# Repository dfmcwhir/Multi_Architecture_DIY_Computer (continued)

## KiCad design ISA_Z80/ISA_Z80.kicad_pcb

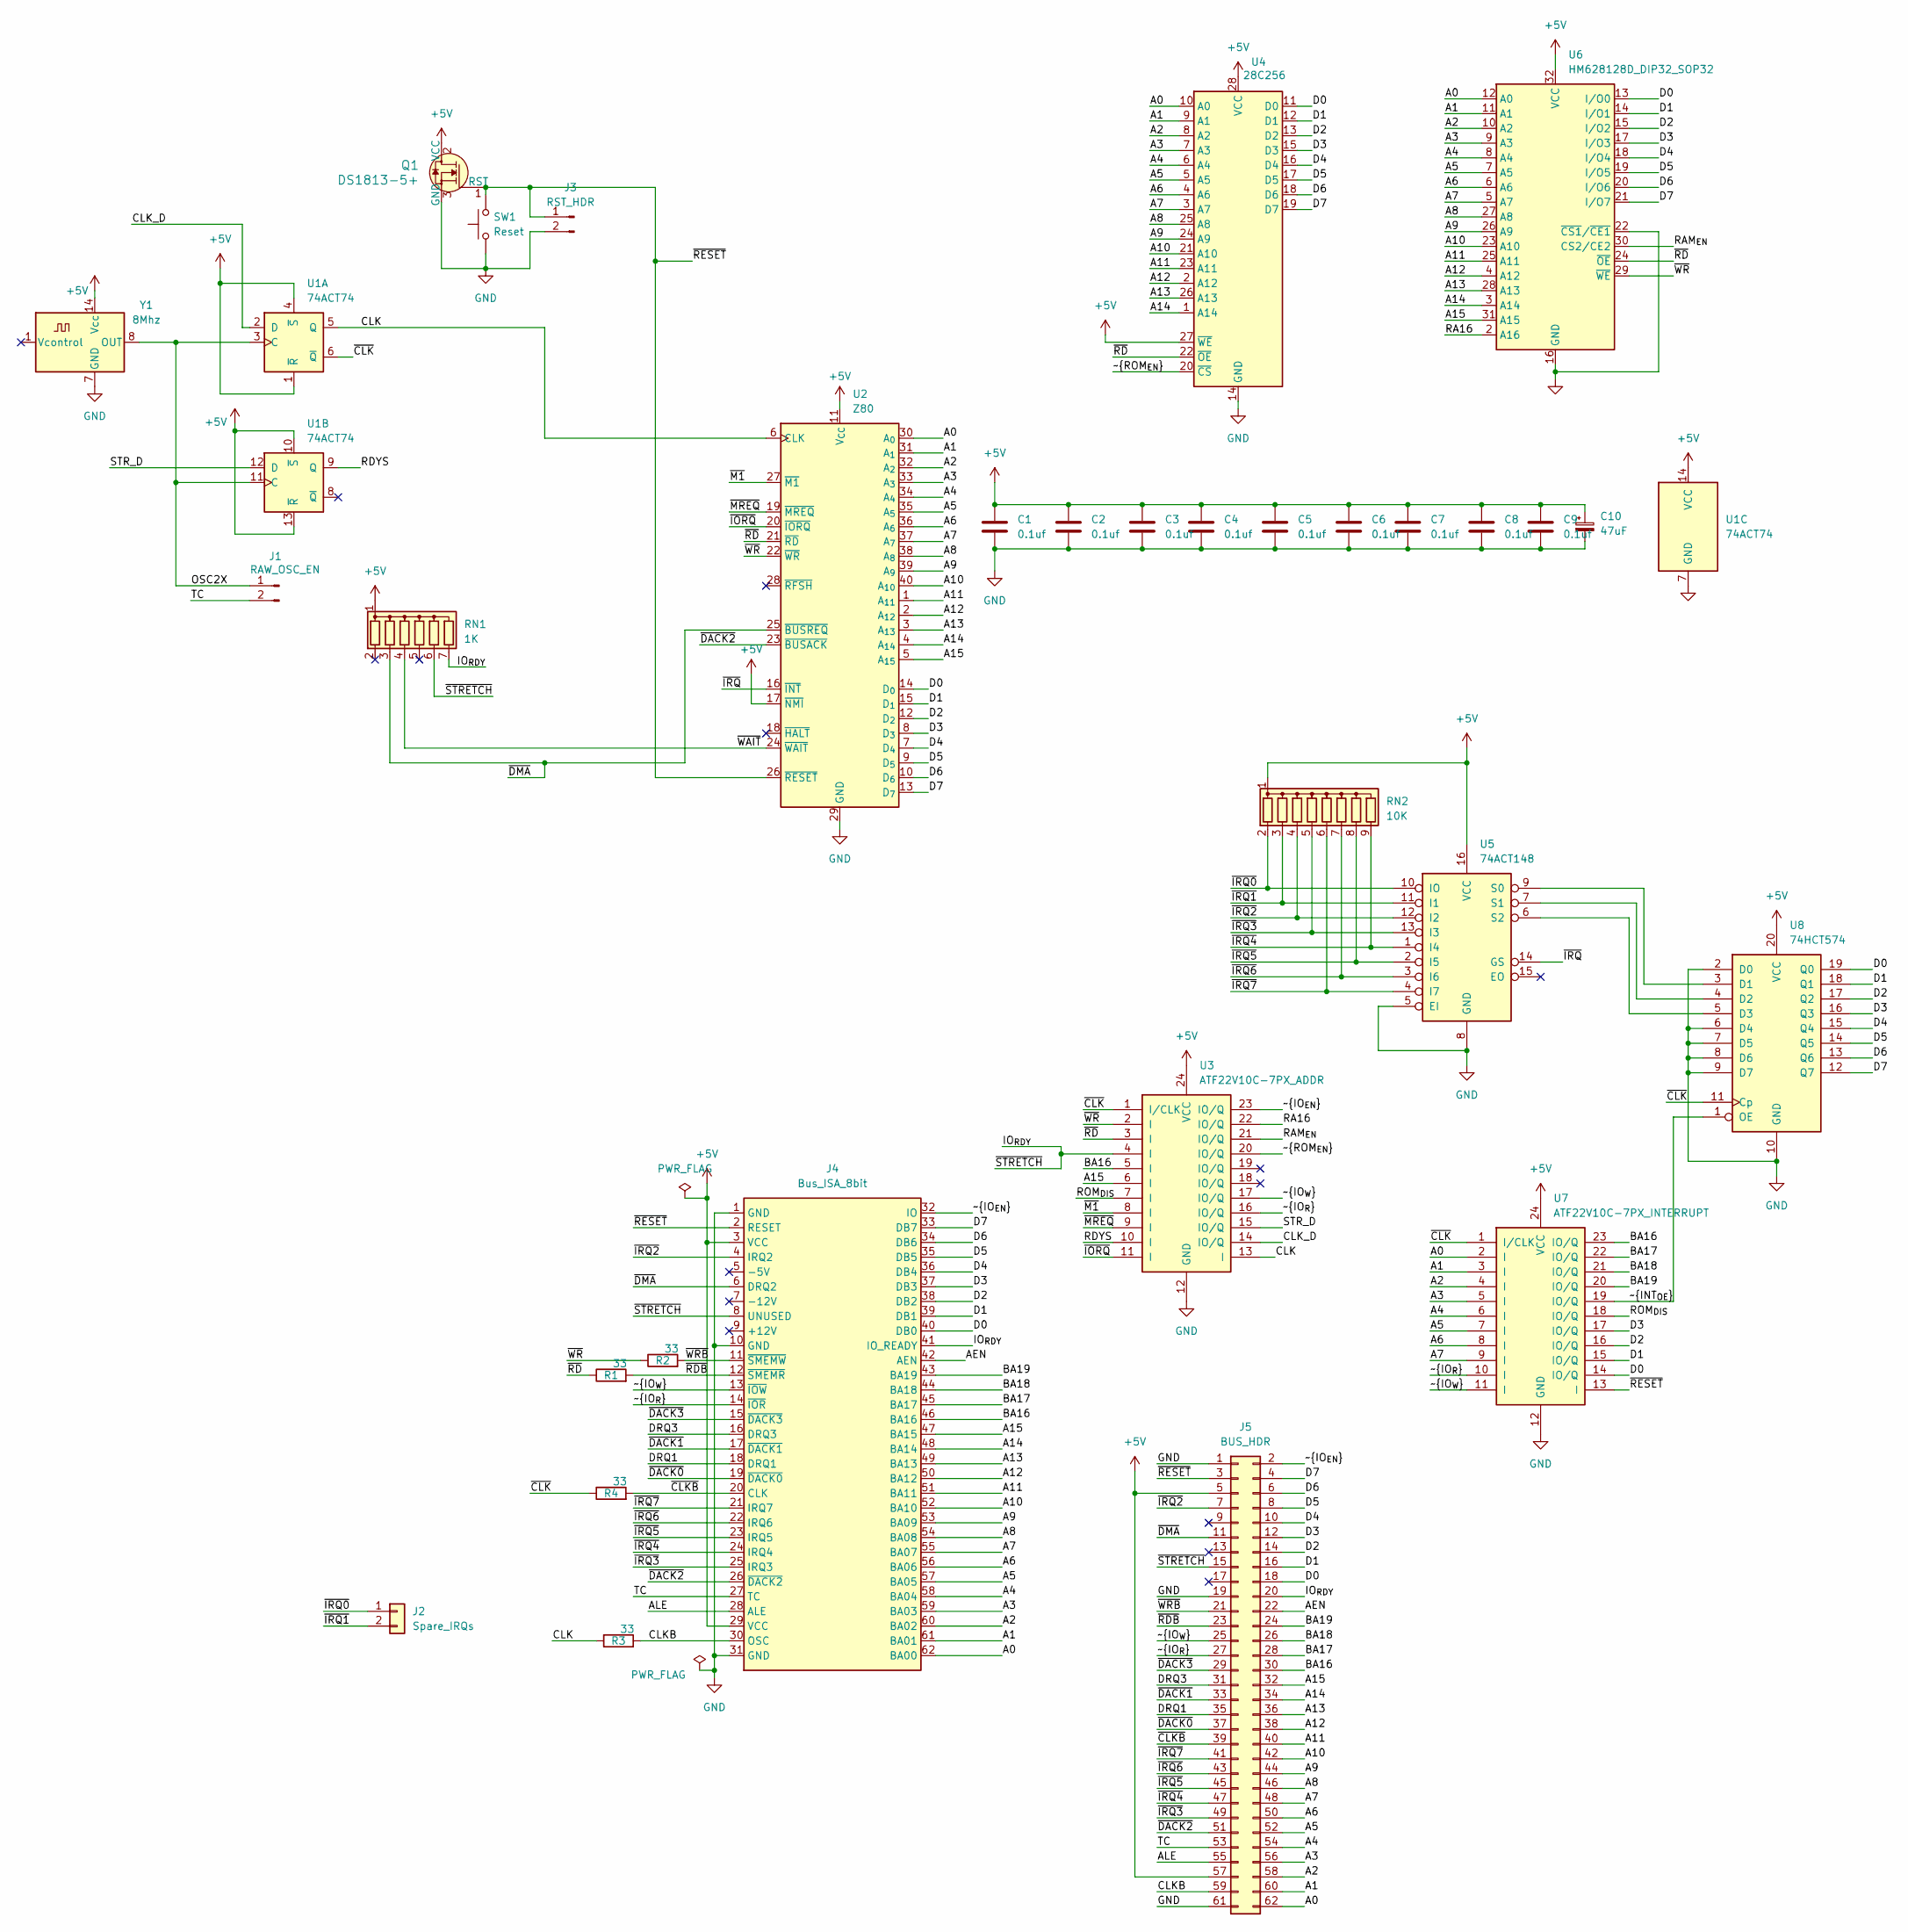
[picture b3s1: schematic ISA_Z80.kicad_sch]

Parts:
C1, C2, C3, C4, C5, C6, C7, C8, C9: 0.1uf; C_Disc_D4.7mm_W2.5mm_P5.00mm
C10: 47uF; CP_Radial_D5.0mm_P2.00mm
J1: RAW_OSC_EN; PinHeader_1x02_P2.54mm_Vertical
J2: Spare_IRQs; PinHeader_1x02_P2.54mm_Vertical
J3: RST_HDR; PinHeader_1x02_P2.54mm_Vertical
J4: Bus_ISA_8bit; BUS_8-bit_ISA
J5: BUS_HDR; PinHeader_2x31_P2.54mm_Vertical
Q1: DS1813-5+; TO-92L_Wide; MPN DS1813-5+-ND; Digi-Key_PN DS1813-5+-ND
R1, R2, R3, R4: 33; R_Axial_DIN0207_L6.3mm_D2.5mm_P10.16mm_Horizontal
RN1: 1K; R_Array_SIP7
RN2: 10K; R_Array_SIP9
SW1: Reset; SW_PUSH_6mm
U1: 74ACT74; DIP-14_W7.62mm
U2: Z80; DIP-40_W15.24mm
U3: ATF22V10C-7PX_ADDR; DIP-24_W7.62mm
U4: 28C256; DIP-28_W15.24mm
U5: 74ACT148; DIP-16_W7.62mm
U6: HM628128D_DIP32_SOP32; DIP-32_W15.24mm
U7: ATF22V10C-7PX_INTERRUPT; DIP-24_W7.62mm
U8: 74HCT574; DIP-20_W7.62mm
Y1: 8Mhz; Oscillator_DIP-14

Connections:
+5V: C1.1, C2.1, C3.1, C4.1, C5.1, C6.1, C7.1, C8.1, C9.1, C10.1, J4.3 (VCC), J4.29 (VCC), J5.5, J5.57, Q1.2 (VCC), RN1.1 (common), RN2.1 (common), U1.1 (~R), U1.4 (~S), U1.10 (~S), U1.13 (~R), U1.14 (VCC), U2.11 (V_{CC}), U2.17 (~NMI), U3.24 (VCC), U4.27 (~WE), U4.28 (VCC), U5.16 (VCC), U6.32 (VCC), U7.24 (VCC), U8.20 (VCC), Y1.14 (Vcc)
/A0: J4.62 (BA00), J5.62, U2.30 (A_{0}), U4.10 (A0), U6.12 (A0), U7.2 (I)
/A1: J4.61 (BA01), J5.60, U2.31 (A_{1}), U4.9 (A1), U6.11 (A1), U7.3 (I)
/A2: J4.60 (BA02), J5.58, U2.32 (A_{2}), U4.8 (A2), U6.10 (A2), U7.4 (I)
/A3: J4.59 (BA03), J5.56, U2.33 (A_{3}), U4.7 (A3), U6.9 (A3), U7.5 (I)
/A4: J4.58 (BA04), J5.54, U2.34 (A_{4}), U4.6 (A4), U6.8 (A4), U7.6 (I)
/A5: J4.57 (BA05), J5.52, U2.35 (A_{5}), U4.5 (A5), U6.7 (A5), U7.7 (I)
/A6: J4.56 (BA06), J5.50, U2.36 (A_{6}), U4.4 (A6), U6.6 (A6), U7.8 (I)
/A7: J4.55 (BA07), J5.48, U2.37 (A_{7}), U4.3 (A7), U6.5 (A7), U7.9 (I)
/A8: J4.54 (BA08), J5.46, U2.38 (A_{8}), U4.25 (A8), U6.27 (A8)
/A9: J4.53 (BA09), J5.44, U2.39 (A_{9}), U4.24 (A9), U6.26 (A9)
/A10: J4.52 (BA10), J5.42, U2.40 (A_{10}), U4.21 (A10), U6.23 (A10)
/A11: J4.51 (BA11), J5.40, U2.1 (A_{11}), U4.23 (A11), U6.25 (A11)
/A12: J4.50 (BA12), J5.38, U2.2 (A_{12}), U4.2 (A12), U6.4 (A12)
/A13: J4.49 (BA13), J5.36, U2.3 (A_{13}), U4.26 (A13), U6.28 (A13)
/A14: J4.48 (BA14), J5.34, U2.4 (A_{14}), U4.1 (A14), U6.3 (A14)
/A15: J4.47 (BA15), J5.32, U2.5 (A_{15}), U3.6 (I), U6.31 (A15)
/AEN: J4.42 (AEN), J5.22
/ALE: J4.28 (ALE), J5.55
/BA16: J4.46 (BA16), J5.30, U3.5 (I), U7.23 (IO/Q)
/BA17: J4.45 (BA17), J5.28, U7.22 (IO/Q)
/BA18: J4.44 (BA18), J5.26, U7.21 (IO/Q)
/BA19: J4.43 (BA19), J5.24, U7.20 (IO/Q)
/CLK: R3.1, U1.5 (Q), U2.6 (CLK), U3.13 (I)
/CLKB: J4.30 (OSC), J5.59, R3.2
/CLK_D: U1.2 (D), U3.14 (IO/Q)
/D0: J4.40 (DB0), J5.18, U2.14 (D_{0}), U4.11 (D0), U6.13 (I/O0), U7.14 (IO/Q), U8.19 (Q0)
/D1: J4.39 (DB1), J5.16, U2.15 (D_{1}), U4.12 (D1), U6.14 (I/O1), U7.15 (IO/Q), U8.18 (Q1)
/D2: J4.38 (DB2), J5.14, U2.12 (D_{2}), U4.13 (D2), U6.15 (I/O2), U7.16 (IO/Q), U8.17 (Q2)
/D3: J4.37 (DB3), J5.12, U2.8 (D_{3}), U4.15 (D3), U6.17 (I/O3), U7.17 (IO/Q), U8.16 (Q3)
/D4: J4.36 (DB4), J5.10, U2.7 (D_{4}), U4.16 (D4), U6.18 (I/O4), U8.15 (Q4)
/D5: J4.35 (DB5), J5.8, U2.9 (D_{5}), U4.17 (D5), U6.19 (I/O5), U8.14 (Q5)
/D6: J4.34 (DB6), J5.6, U2.10 (D_{6}), U4.18 (D6), U6.20 (I/O6), U8.13 (Q6)
/D7: J4.33 (DB7), J5.4, U2.13 (D_{7}), U4.19 (D7), U6.21 (I/O7), U8.12 (Q7)
/DRQ1: J4.18 (DRQ1), J5.35
/DRQ3: J4.16 (DRQ3), J5.31
/IO_{RDY}: J4.8 (UNUSED), J4.41 (IO_READY), J5.15, J5.20, RN1.6 (R5), RN1.7 (R6), U3.4 (I)
/OSC2X: J1.1, U1.3 (C), U1.11 (C), Y1.8 (OUT)
/RA16: U3.22 (IO/Q), U6.2 (A16)
/RAM_{EN}: U3.21 (IO/Q), U6.30 (CS2/CE2)
/RDYS: U1.9 (Q), U3.10 (I)
/ROM_{DIS}: U3.7 (I), U7.18 (IO/Q)
/STR_D: U1.12 (D), U3.15 (IO/Q)
/TC: J1.2, J4.27 (TC), J5.53
/~CLKB: J4.20 (CLK), J5.39, R4.2
/~CLK: R4.1, U1.6 (~Q), U3.1 (I/CLK), U7.1 (I/CLK), U8.11 (Cp)
/~DACK0: J4.19 (~DACK0), J5.37
/~DACK1: J4.17 (~DACK1), J5.33
/~DACK2: J4.26 (~DACK2), J5.51, U2.23 (~BUSACK)
/~DACK3: J4.15 (~DACK3), J5.29
/~DMA: J4.6 (DRQ2), J5.11, RN1.3 (R2), U2.25 (~BUSREQ)
/~INT_{OE}: U7.19 (IO/Q), U8.1 (OE)
/~IORQ: U2.20 (~IORQ), U3.11 (I)
/~IO_{EN}: J4.32 (IO), J5.2, U3.23 (IO/Q)
/~IO_{R}: J4.14 (~IOR), J5.27, U3.16 (IO/Q), U7.10 (I)
/~IO_{W}: J4.13 (~IOW), J5.25, U3.17 (IO/Q), U7.11 (I)
/~IRQ0: J2.1, RN2.2 (R1), U5.10 (IO)
/~IRQ1: J2.2, RN2.3 (R2), U5.11 (I1)
/~IRQ2: J4.4 (IRQ2), J5.7, RN2.4 (R3), U5.12 (I2)
/~IRQ3: J4.25 (IRQ3), J5.49, RN2.5 (R4), U5.13 (I3)
/~IRQ4: J4.24 (IRQ4), J5.47, RN2.9 (R8), U5.1 (I4)
/~IRQ5: J4.23 (IRQ5), J5.45, RN2.8 (R7), U5.2 (I5)
/~IRQ6: J4.22 (IRQ6), J5.43, RN2.7 (R6), U5.3 (I6)
/~IRQ7: J4.21 (IRQ7), J5.41, RN2.6 (R5), U5.4 (I7)
/~IRQ: U2.16 (~INT), U5.14 (GS)
/~M1: U2.27 (~M1), U3.8 (I)
/~MREQ: U2.19 (~MREQ), U3.9 (I)
/~RDB: J4.12 (~SMEMR), J5.23, R1.2
/~RD: R1.1, U2.21 (~RD), U3.3 (I), U4.22 (~OE), U6.24 (~OE)
/~RESET: J3.1, J4.2 (RESET), J5.3, Q1.1 (RST), SW1.2, U2.26 (~RESET), U7.13 (I)
/~ROM_{EN}: U3.20 (IO/Q), U4.20 (~CS)
/~WAIT: RN1.4 (R3), U2.24 (~WAIT)
/~WRB: J4.11 (~SMEMW), J5.21, R2.2
/~WR: R2.1, U2.22 (~WR), U3.2 (I), U6.29 (~WE)
GND: C1.2, C2.2, C3.2, C4.2, C5.2, C6.2, C7.2, C8.2, C9.2, C10.2, J3.2, J4.1 (GND), J4.10 (GND), J4.31 (GND), J5.1, J5.19, J5.61, Q1.3 (GND), SW1.1, U1.7 (GND), U2.29 (GND), U3.12 (GND), U4.14 (GND), U5.5 (EI), U5.8 (GND), U6.16 (GND), U6.22 (~CS1/~CE1), U7.12 (GND), U8.2 (D0), U8.6 (D4), U8.7 (D5), U8.8 (D6), U8.9 (D7), U8.10 (GND), Y1.7 (GND)
unnamed: U5.9 (S0), U8.3 (D1)
unnamed: U5.7 (S1), U8.4 (D2)
unnamed: U5.6 (S2), U8.5 (D3)

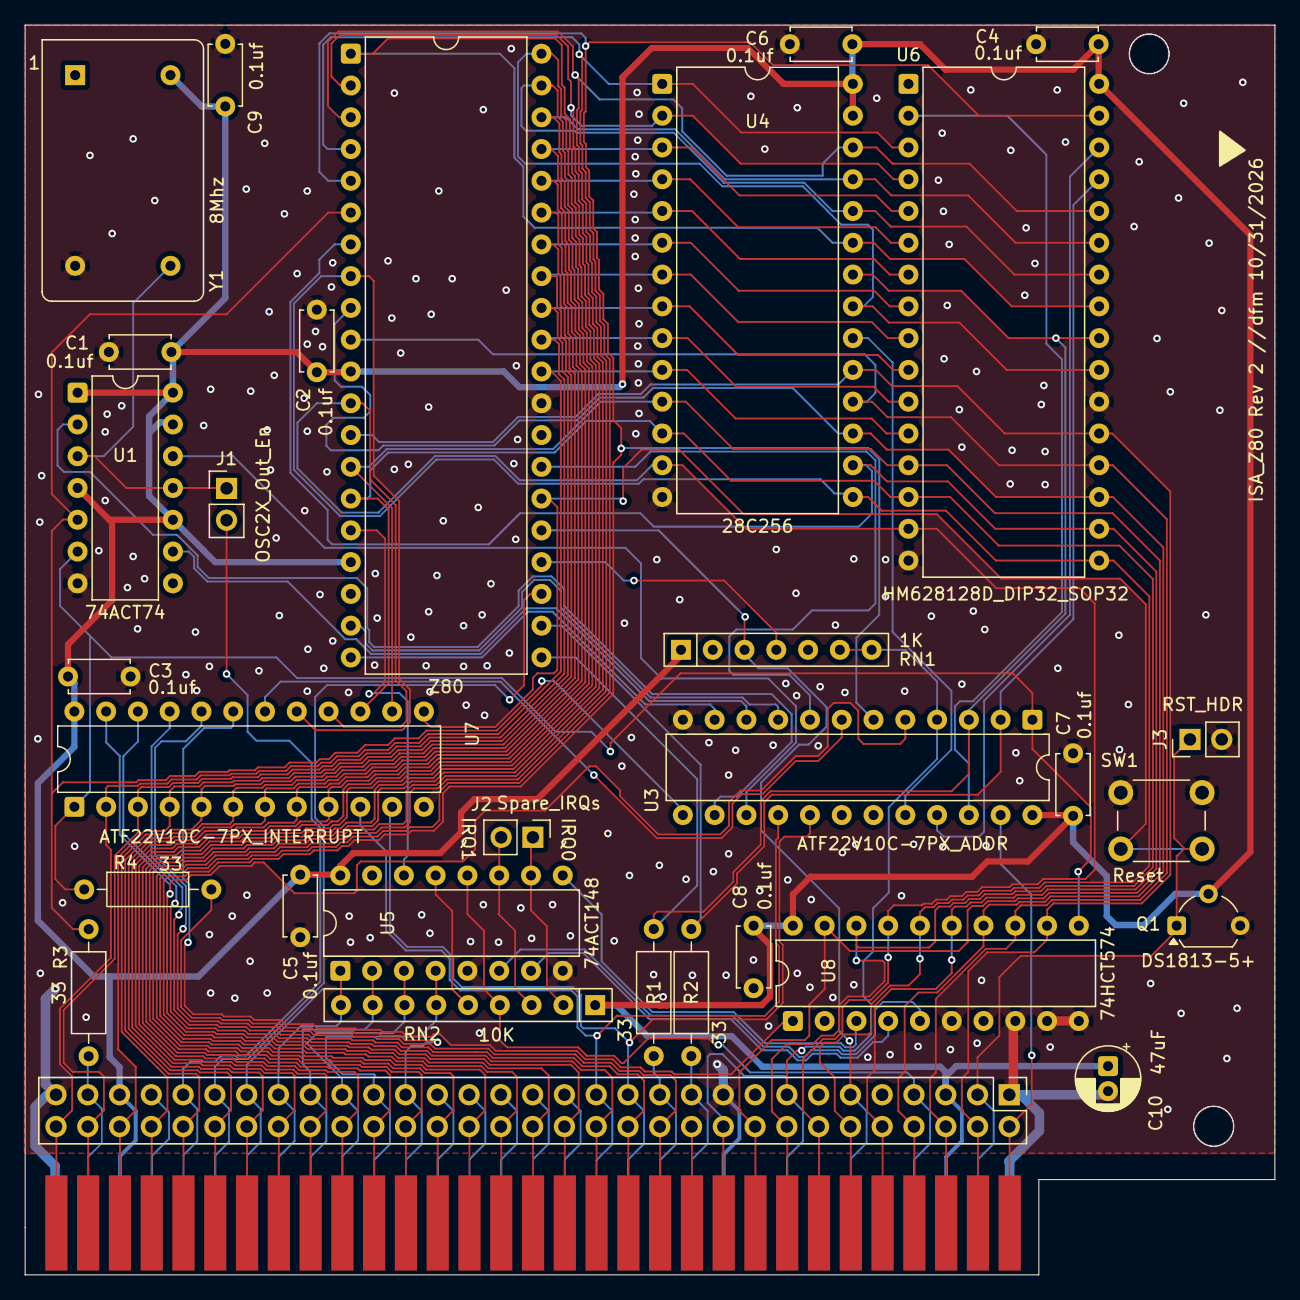
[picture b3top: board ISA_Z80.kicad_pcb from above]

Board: 2 copper layers, 99.9 x 99.9 mm, 32 parts (0 on the bottom side), 78 nets.

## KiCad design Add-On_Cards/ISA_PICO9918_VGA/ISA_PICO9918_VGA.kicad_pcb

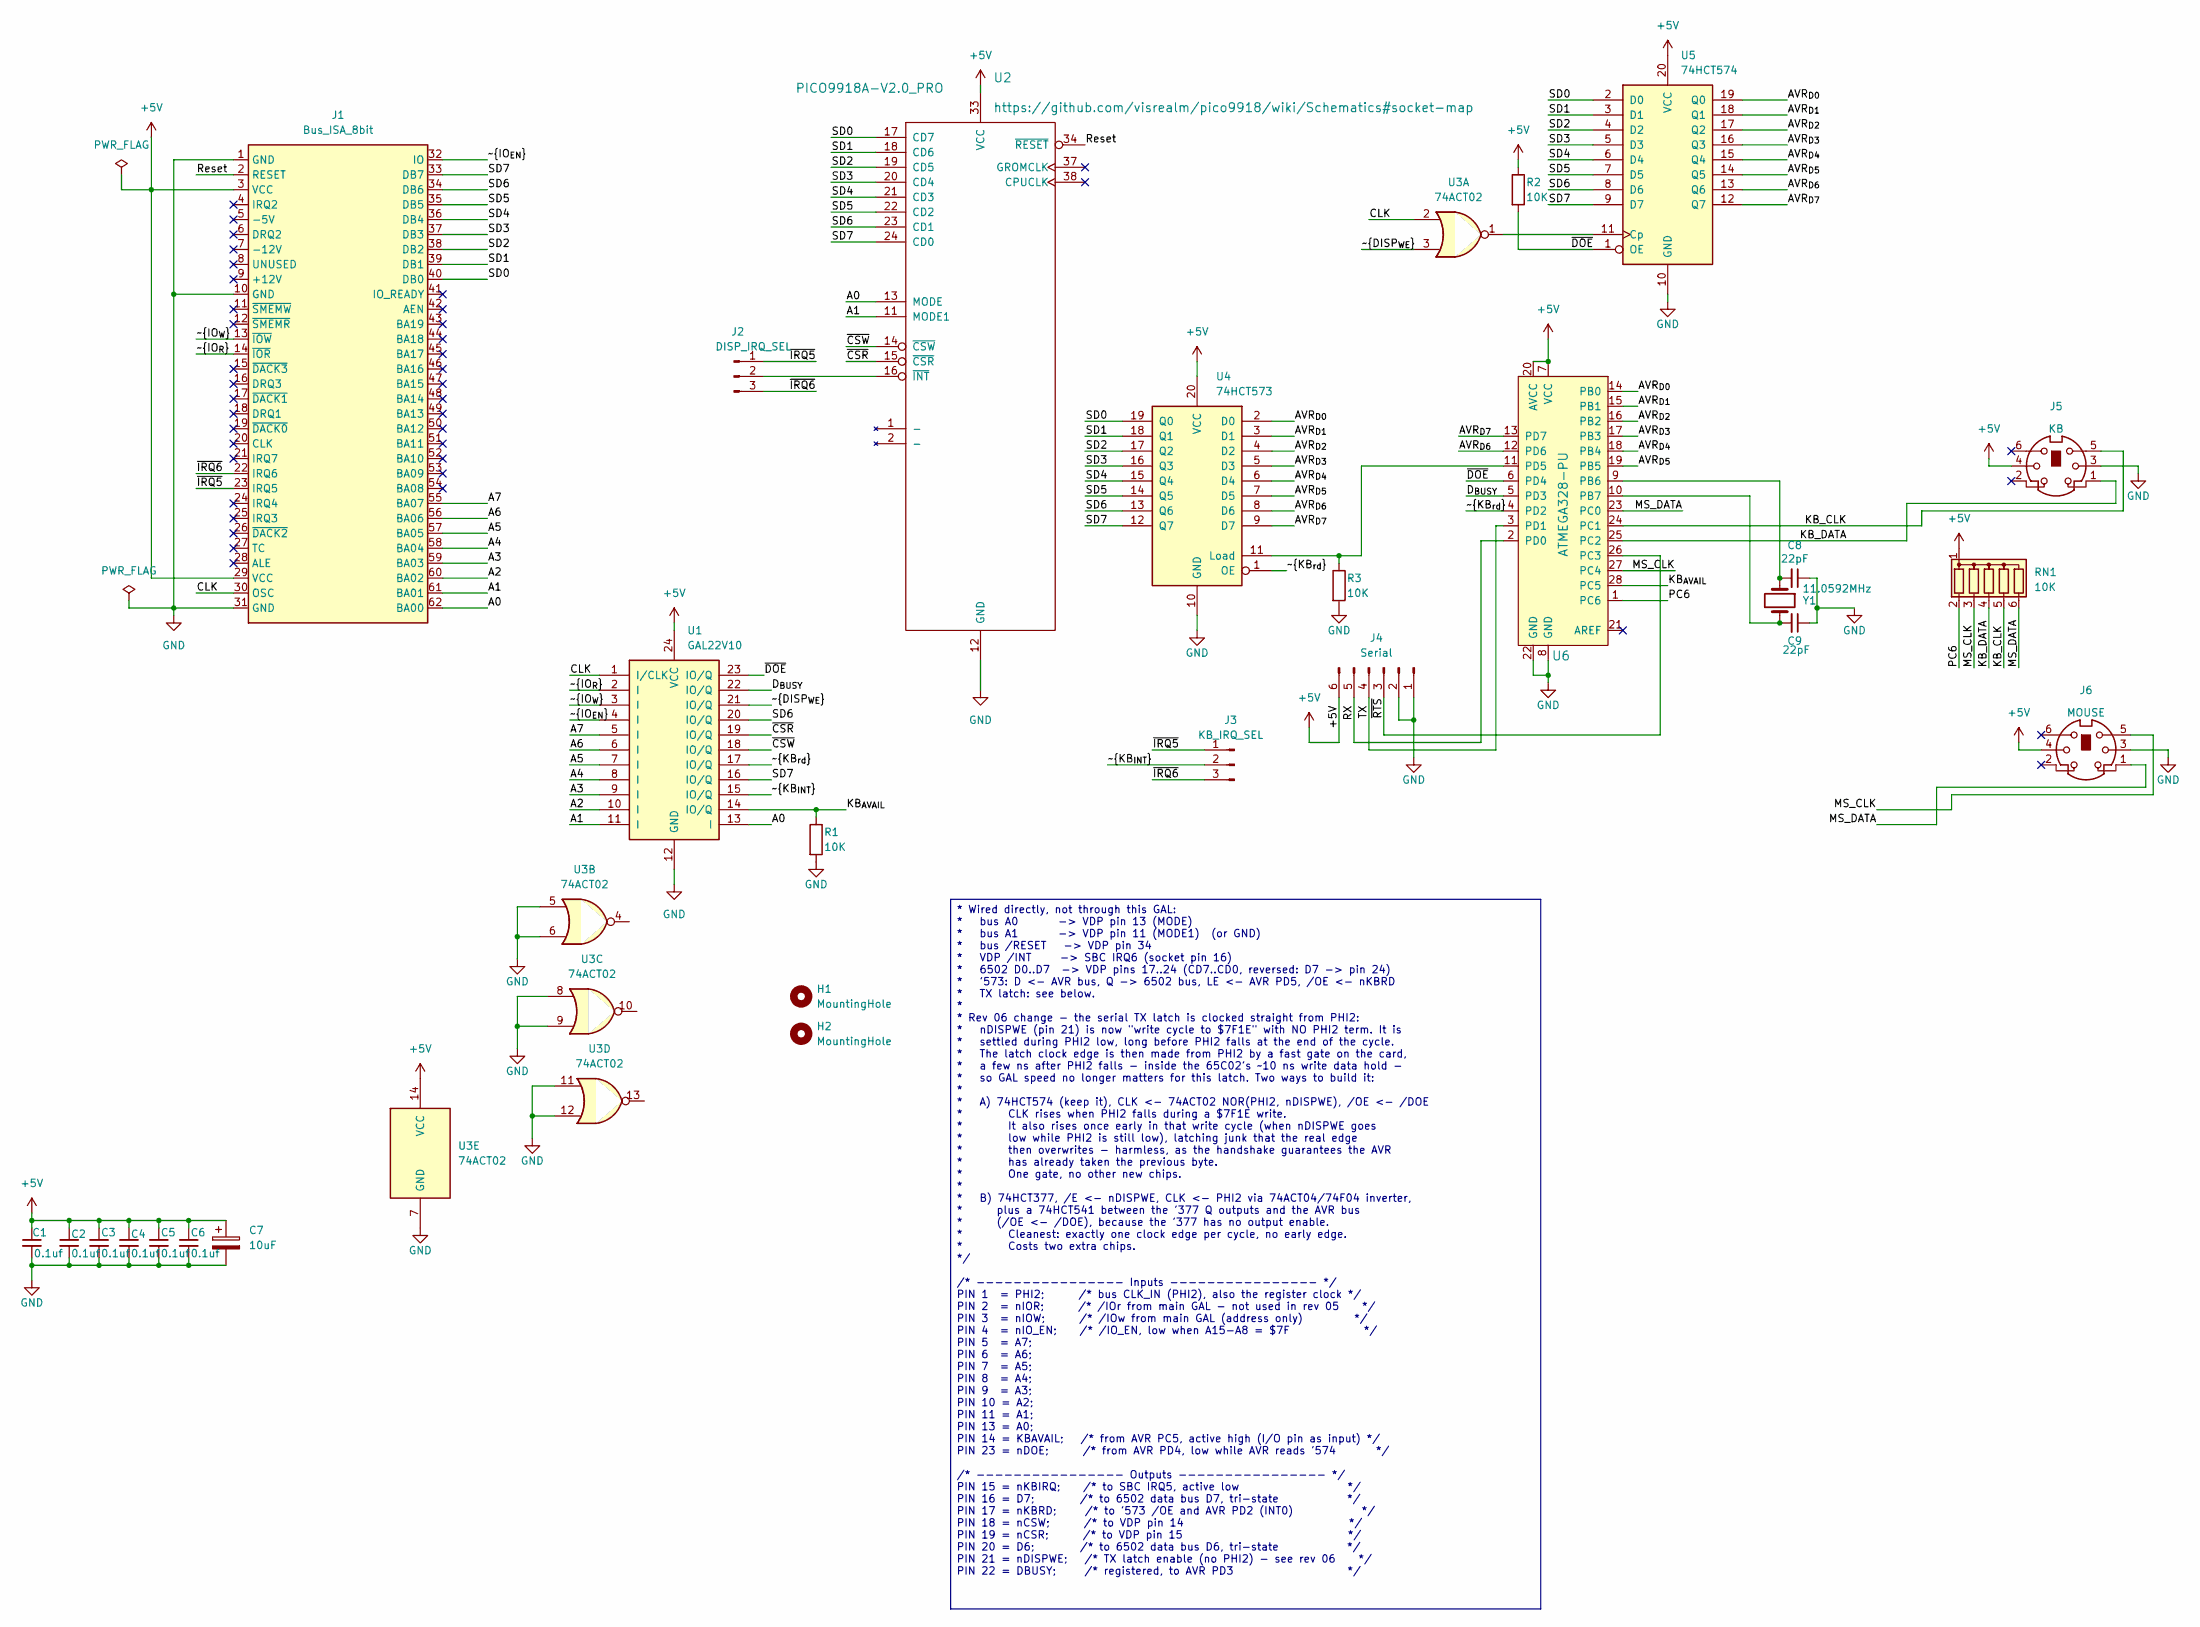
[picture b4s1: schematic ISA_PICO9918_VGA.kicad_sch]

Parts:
C1, C2, C3, C4, C5, C6: 0.1uf; C_Disc_D4.7mm_W2.5mm_P5.00mm; Voltage 50V; Tolerance 5%
C7: 10uF; CP_Radial_D5.0mm_P2.00mm
C8, C9: 22pF; C_Disc_D4.7mm_W2.5mm_P5.00mm; Voltage 50V; Tolerance 5%
H1, H2: MountingHole; MountingHole_3.2mm_M3
J1: Bus_ISA_8bit; BUS_8-bit_ISA_CARD
J2: DISP_IRQ_SEL; PinHeader_1x03_P2.54mm_Vertical
J3: KB_IRQ_SEL; PinHeader_1x03_P2.54mm_Vertical
J4: Serial; PinHeader_1x06_P2.54mm_Vertical
J5: KB; Connector_Mini-DIN_Female_6Pin_2rows
J6: MOUSE; Connector_Mini-DIN_Female_6Pin_2rows
R1, R2, R3: 10K; R_Axial_DIN0207_L6.3mm_D2.5mm_P10.16mm_Horizontal
RN1: 10K; R_Array_SIP6
U1: GAL22V10; DIP-24_W7.62mm
U2: PICO9918A-V2.0_PRO; DIP-40_W15.24mm
U3: 74ACT02; DIP-14_W7.62mm
U4: 74HCT573; DIP-20_W7.62mm
U5: 74HCT574; DIP-20_W7.62mm
U6: ATMEGA328-PU; DIP-28_W7.62mm_Socket; MPN ATMEGA328-PU; Digi-Key_PN ATMEGA328-PU-ND
Y1: 11.0592MHz; Crystal_HC18-U_Vertical

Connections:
+5V: C1.1, C2.1, C3.1, C4.1, C5.1, C6.1, C7.1, J1.3 (VCC), J1.29 (VCC), J4.6, J5.4, J6.4, R2.1, RN1.1 (common), U1.24 (VCC), U2.33 (VCC), U3.14 (VCC), U4.20 (VCC), U5.20 (VCC), U6.7 (VCC), U6.20 (AVCC)
/A0: J1.62 (BA00), U1.13 (I), U2.13 (MODE)
/A1: J1.61 (BA01), U1.11 (I), U2.11 (MODE1)
/A2: J1.60 (BA02), U1.10 (I)
/A3: J1.59 (BA03), U1.9 (I)
/A4: J1.58 (BA04), U1.8 (I)
/A5: J1.57 (BA05), U1.7 (I)
/A6: J1.56 (BA06), U1.6 (I)
/A7: J1.55 (BA07), U1.5 (I)
/AVR_{D0}: U4.2 (D0), U5.19 (Q0), U6.14 (PB0)
/AVR_{D1}: U4.3 (D1), U5.18 (Q1), U6.15 (PB1)
/AVR_{D2}: U4.4 (D2), U5.17 (Q2), U6.16 (PB2)
/AVR_{D3}: U4.5 (D3), U5.16 (Q3), U6.17 (PB3)
/AVR_{D4}: U4.6 (D4), U5.15 (Q4), U6.18 (PB4)
/AVR_{D5}: U4.7 (D5), U5.14 (Q5), U6.19 (PB5)
/AVR_{D6}: U4.8 (D6), U5.13 (Q6), U6.12 (PD6)
/AVR_{D7}: U4.9 (D7), U5.12 (Q7), U6.13 (PD7)
/CLK: J1.30 (OSC), U1.1 (I/CLK), U3.2
/D_{BUSY}: U1.22 (IO/Q), U6.5 (PD3)
/KB_CLK: J5.5, RN1.5 (R4), U6.24 (PC1)
/KB_DATA: J5.1, RN1.4 (R3), U6.25 (PC2)
/KB_{AVAIL}: R1.1, U1.14 (IO/Q), U6.28 (PC5)
/MS_CLK: J6.5, RN1.3 (R2), U6.27 (PC4)
/MS_DATA: J6.1, RN1.6 (R5), U6.23 (PC0)
/PC6: RN1.2 (R1), U6.1 (PC6)
/RX: J4.5, U6.2 (PD0)
/Reset: J1.2 (RESET), U2.34 (~RESET)
/SD0: J1.40 (DB0), U2.17 (CD7), U4.19 (Q0), U5.2 (D0)
/SD1: J1.39 (DB1), U2.18 (CD6), U4.18 (Q1), U5.3 (D1)
/SD2: J1.38 (DB2), U2.19 (CD5), U4.17 (Q2), U5.4 (D2)
/SD3: J1.37 (DB3), U2.20 (CD4), U4.16 (Q3), U5.5 (D3)
/SD4: J1.36 (DB4), U2.21 (CD3), U4.15 (Q4), U5.6 (D4)
/SD5: J1.35 (DB5), U2.22 (CD2), U4.14 (Q5), U5.7 (D5)
/SD6: J1.34 (DB6), U1.20 (IO/Q), U2.23 (CD1), U4.13 (Q6), U5.8 (D6)
/SD7: J1.33 (DB7), U1.16 (IO/Q), U2.24 (CD0), U4.12 (Q7), U5.9 (D7)
/TX: J4.4, U6.3 (PD1)
/~CSR: U1.19 (IO/Q), U2.15 (~CSR)
/~CSW: U1.18 (IO/Q), U2.14 (~CSW)
/~DISP_{WE}: U1.21 (IO/Q), U3.3
/~DOE: R2.2, U1.23 (IO/Q), U5.1 (OE), U6.6 (PD4)
/~IO_{EN}: J1.32 (IO), U1.4 (I)
/~IO_{R}: J1.14 (~IOR), U1.2 (I)
/~IO_{W}: J1.13 (~IOW), U1.3 (I)
/~IRQ5: J1.23 (IRQ5), J2.1, J3.1
/~IRQ6: J1.22 (IRQ6), J2.3, J3.3
/~KB_{INT}: J3.2, U1.15 (IO/Q)
/~KB_{rd}: U1.17 (IO/Q), U4.1 (OE), U6.4 (PD2)
/~RTS: J4.3, U6.26 (PC3)
GND: C1.2, C2.2, C3.2, C4.2, C5.2, C6.2, C7.2, C8.1, C9.1, J1.1 (GND), J1.10 (GND), J1.31 (GND), J4.1, J4.2, J5.3, J6.3, R1.2, R3.2, U1.12 (GND), U2.12 (GND), U3.5, U3.6, U3.7 (GND), U3.8, U3.9, U3.11, U3.12, U4.10 (GND), U5.10 (GND), U6.8 (GND), U6.22 (GND)
unnamed: J2.2, U2.16 (~INT)
unnamed: R3.1, U4.11 (Load), U6.11 (PD5)
unnamed: U3.1, U5.11 (Cp)
unnamed: C8.2, U6.9 (PB6), Y1.1
unnamed: C9.2, U6.10 (PB7), Y1.2

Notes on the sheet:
* Wired directly, not through this GAL: * bus A0 -> VDP pin 13 (MODE) * bus A1 -> VDP pin 11 (MODE1) (or GND) * bus /RESET -> VDP pin 34 * VDP /INT -> SBC IRQ6 (socket pin 16) * 6502 D0..D7 -> VDP pins 17..24 (CD7..CD0, reversed: D7 -> pin 24) * '573: D <- AVR bus, Q -> 6502 bus, LE <- AVR PD5, /OE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

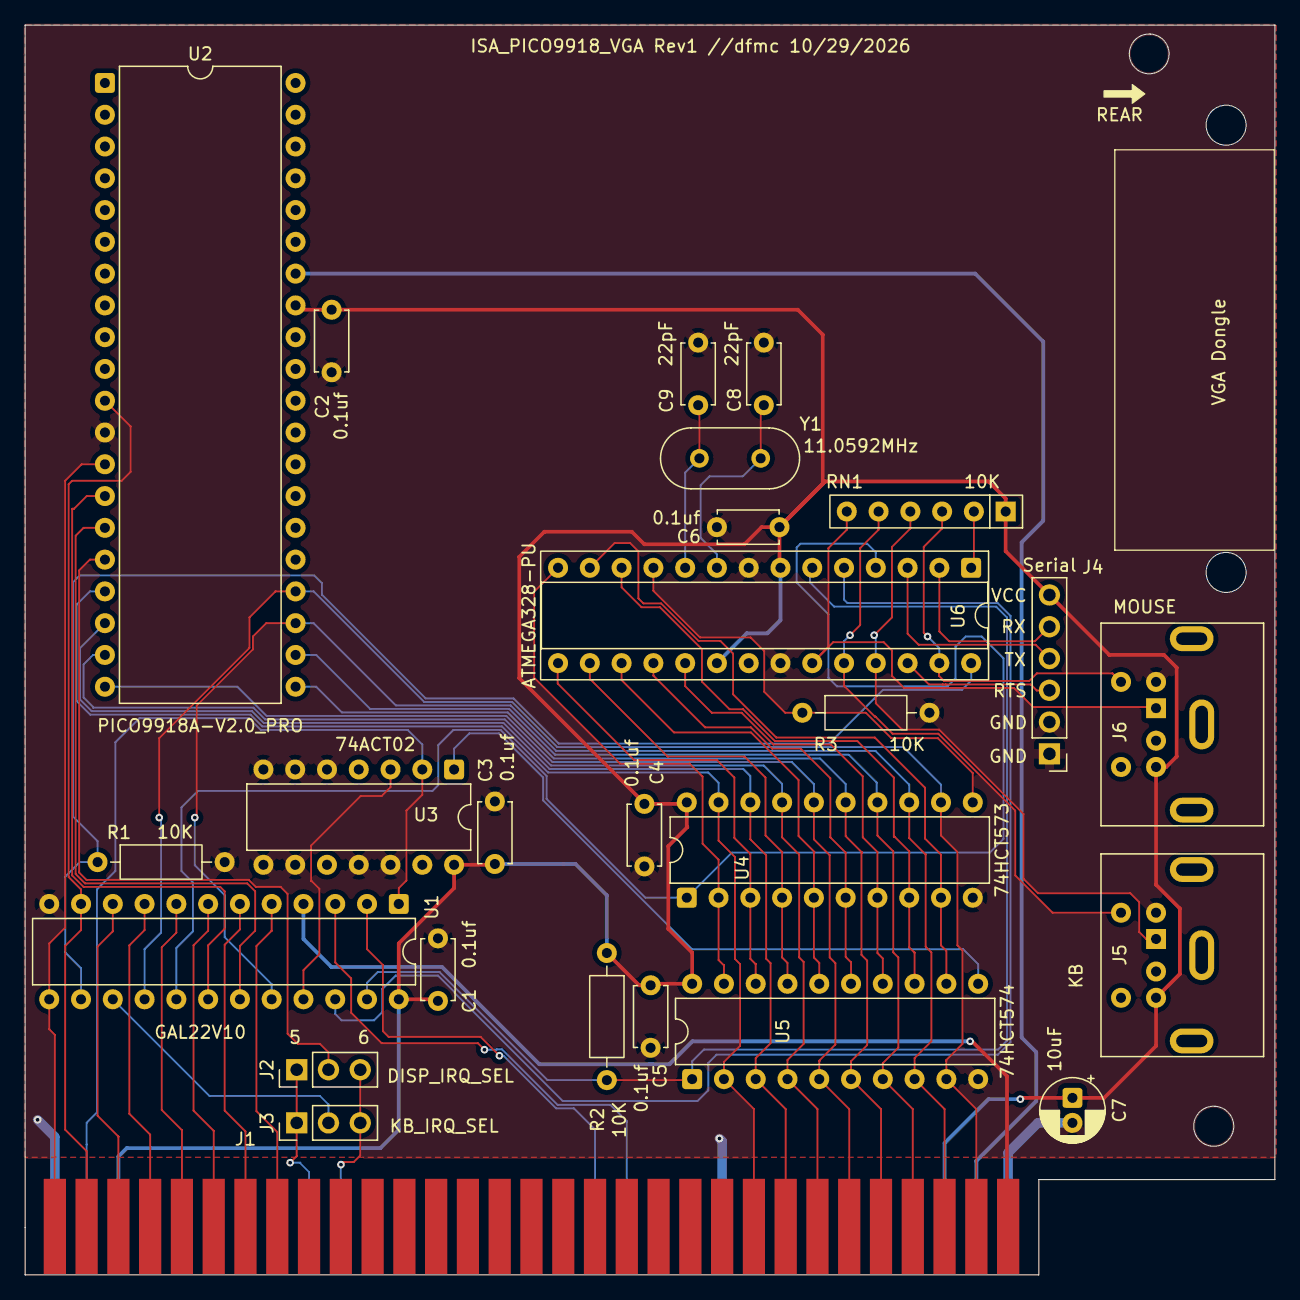
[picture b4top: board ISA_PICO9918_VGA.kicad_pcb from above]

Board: 2 copper layers, 99.9 x 99.9 mm, 28 parts (0 on the bottom side), 54 nets.

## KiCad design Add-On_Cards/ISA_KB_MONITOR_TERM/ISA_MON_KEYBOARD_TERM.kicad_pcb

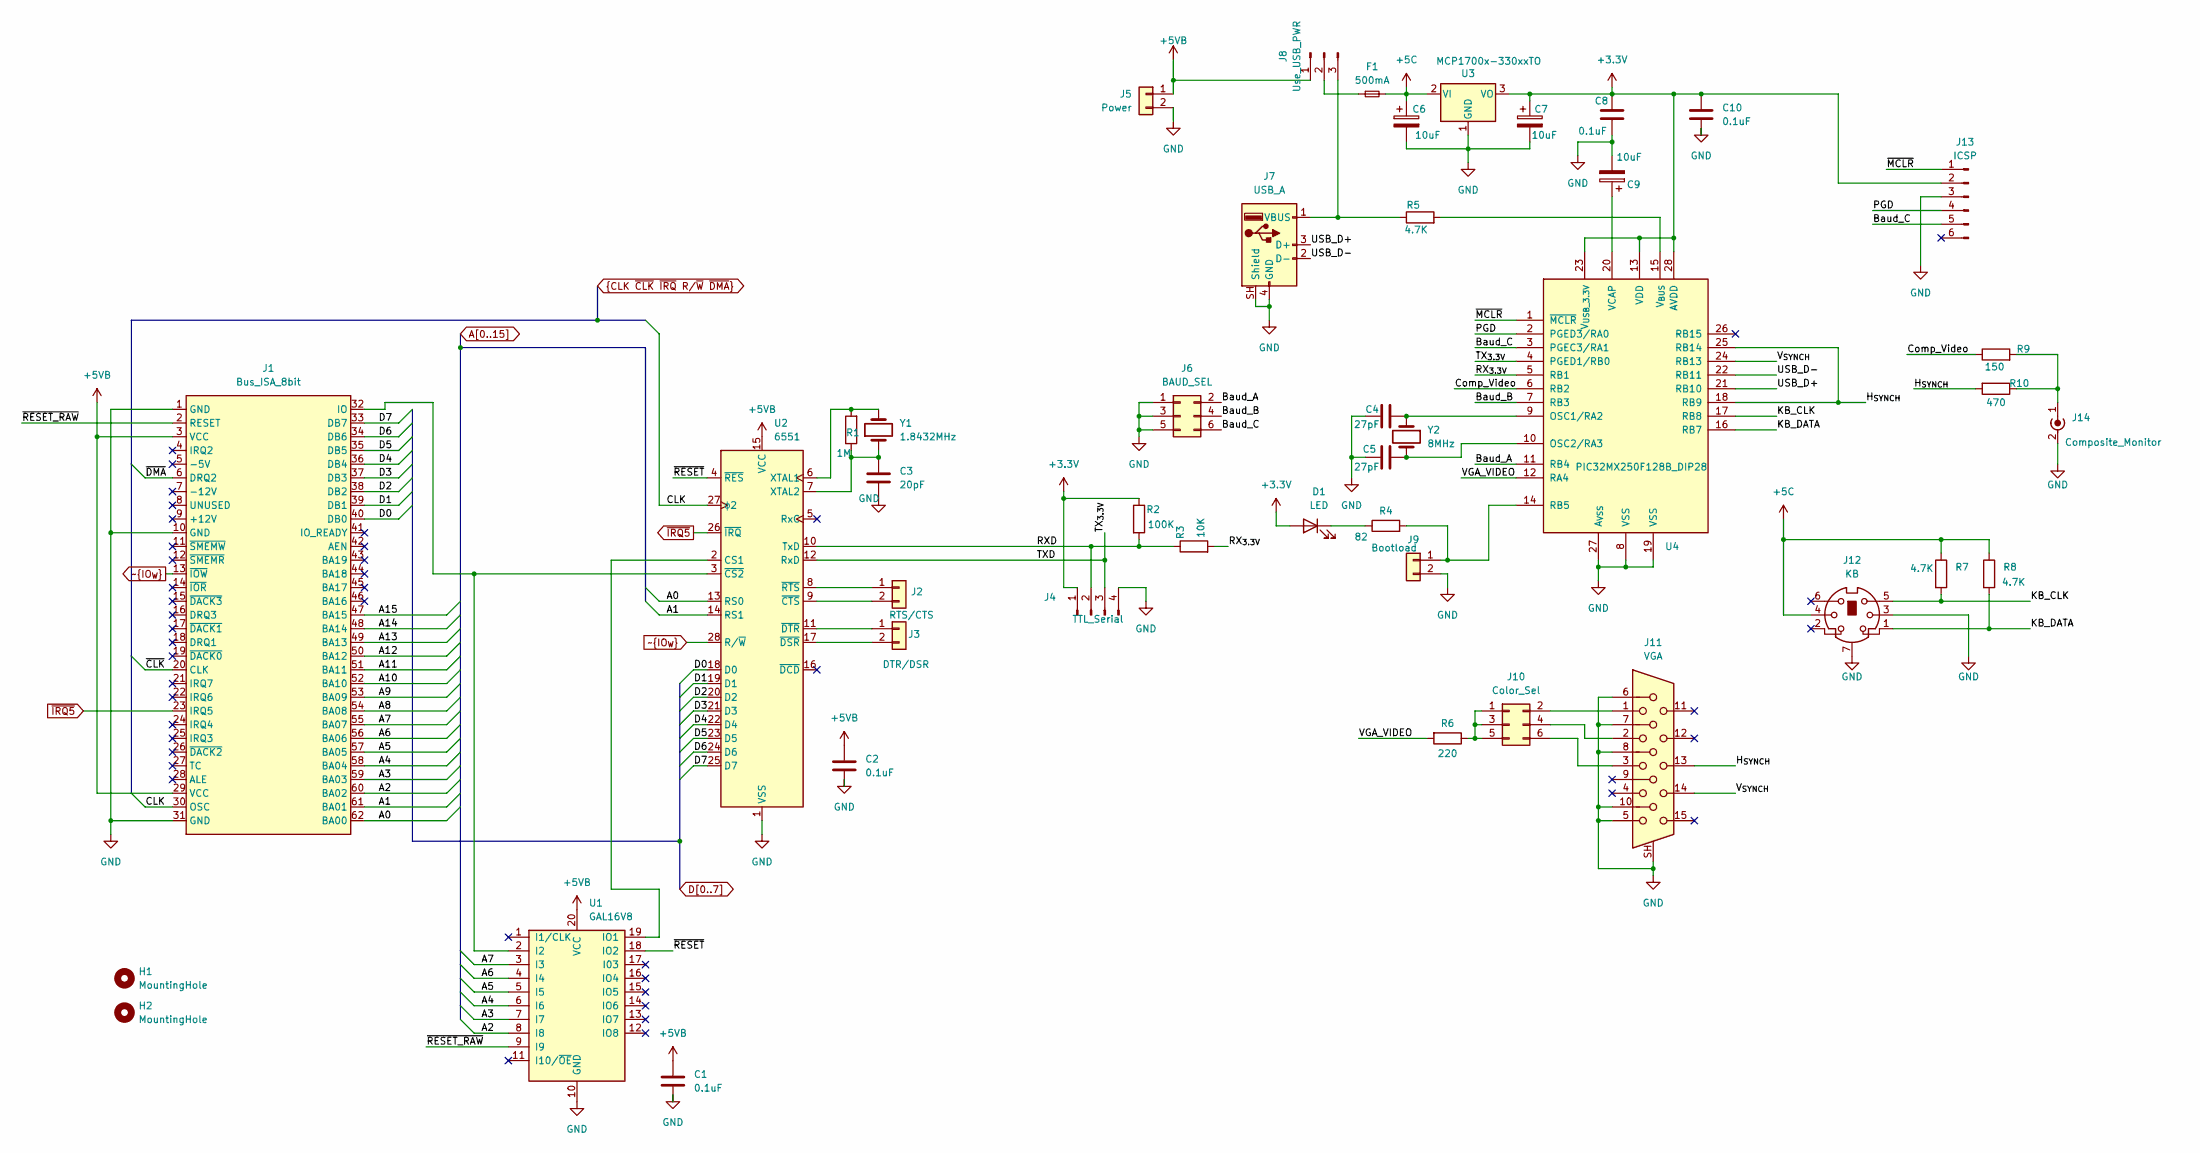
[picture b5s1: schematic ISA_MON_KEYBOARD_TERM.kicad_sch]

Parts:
C1, C2, C8, C10: 0.1uF; C_Disc_D4.7mm_W2.5mm_P5.00mm
C3: 20pF; C_Disc_D4.7mm_W2.5mm_P5.00mm
C4, C5: 27pF; C_Disc_D4.7mm_W2.5mm_P5.00mm
C6, C7, C9: 10uF; CP_Radial_D5.0mm_P2.50mm
D1: LED; LED_D5.0mm
F1: 500mA; R_Axial_DIN0207_L6.3mm_D2.5mm_P10.16mm_Horizontal
H1, H2: MountingHole; MountingHole_3.2mm_M3
J1: Bus_ISA_8bit; BUS_8-bit_ISA
J2: RTS/CTS; PinHeader_1x02_P2.54mm_Vertical
J3: DTR/DSR; PinHeader_1x02_P2.54mm_Vertical
J4: TTL_Serial; PinHeader_1x04_P2.54mm_Vertical
J5: Power; PinHeader_1x02_P2.54mm_Vertical
J6: BAUD_SEL; PinHeader_2x03_P2.54mm_Vertical
J7: USB_A; USB_A_Connfly_DS1095
J8: Use_USB_PWR; PinHeader_1x03_P2.54mm_Vertical
J9: Bootload; PinHeader_1x02_P2.54mm_Vertical
J10: Color_Sel; PinHeader_2x03_P2.54mm_Vertical
J11: VGA; DSUB-15-HD_Socket_Horizontal_P2.29x1.90mm_EdgePinOffset3.03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
J12: KB; Connector_Mini-DIN_Female_6Pin_2rows
J13: ICSP; PinHeader_1x06_P2.54mm_Vertical
J14: Composite_Monitor; RCA_JACK_Right_Angle_AliExpress
R1: 1M; R_Axial_DIN0207_L6.3mm_D2.5mm_P10.16mm_Horizontal
R2: 100K; R_Axial_DIN0207_L6.3mm_D2.5mm_P10.16mm_Horizontal
R3: 10K; R_Axial_DIN0207_L6.3mm_D2.5mm_P10.16mm_Horizontal
R4: 82; R_Axial_DIN0207_L6.3mm_D2.5mm_P10.16mm_Horizontal
R5, R7, R8: 4.7K; R_Axial_DIN0207_L6.3mm_D2.5mm_P10.16mm_Horizontal
R6: 220; R_Axial_DIN0207_L6.3mm_D2.5mm_P10.16mm_Horizontal
R9: 150; R_Axial_DIN0207_L6.3mm_D2.5mm_P10.16mm_Horizontal
R10: 470; R_Axial_DIN0207_L6.3mm_D2.5mm_P10.16mm_Horizontal
U1: GAL16V8; DIP-20_W7.62mm
U2: 6551; DIP-28_W15.24mm
U3: MCP1700x-330xxTO; TO-92_Wide
U4: PIC32MX250F128B_DIP28; DIP-28_W7.62mm
Y1: 1.8432MHz; Crystal_HC18-U_Vertical
Y2: 8MHz; Crystal_HC18-U_Vertical

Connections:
+3.3V: C7.1, C8.1, C10.1, D1.2 (A), J4.1, J13.2, R2.1, U3.3 (VO), U4.13 (VDD), U4.23 (V_{USB_3.3V}), U4.28 (AVDD)
+5C: C6.1, F1.2, J12.4, R7.1, R8.1, U3.2 (VI)
+5VB: C1.1, C2.1, J1.3 (VCC), J1.29 (VCC), J5.1, J8.1, U1.20 (VCC), U2.15 (VCC)
/Baud_A: J6.2, U4.11 (RB4)
/Baud_B: J6.4, U4.7 (RB3)
/Baud_C: J6.6, J13.5, U4.3 (PGEC3/RA1)
/Comp_Video: R9.1, U4.6 (RB2)
/H_{SYNCH}: J11.13, R10.2, U4.18 (RB9), U4.25 (RB14)
/KB_CLK: J12.5, R7.2, U4.17 (RB8)
/KB_DATA: J12.1, R8.2, U4.16 (RB7)
/PGD: J13.4, U4.2 (PGED3/RA0)
/RXD: J4.2, R2.2, R3.1, U2.10 (TxD)
/RX_{3.3V}: R3.2, U4.5 (RB1)
/TXD: J4.3, U2.12 (RxD), U4.4 (PGED1/RB0)
/USB_D+: J7.3 (D+), U4.21 (RB10)
/USB_D-: J7.2 (D-), U4.22 (RB11)
/VGA_VIDEO: R6.2, U4.12 (RA4)
/V_{SYNCH}: J11.14, U4.24 (RB13)
/~MCLR: J13.1, U4.1 (~MCLR)
/~RESET_RAW: J1.2 (RESET), U1.9 (I9)
/~RESET: U1.18 (IO2), U2.4 (~RES)
A0: J1.62 (BA00), U2.13 (RS0)
A1: J1.61 (BA01), U2.14 (RS1)
A2: J1.60 (BA02), U1.8 (I8)
A3: J1.59 (BA03), U1.7 (I7)
A4: J1.58 (BA04), U1.6 (I6)
A5: J1.57 (BA05), U1.5 (I5)
A6: J1.56 (BA06), U1.4 (I4)
A7: J1.55 (BA07), U1.3 (I3)
A8: J1.54 (BA08)
A9: J1.53 (BA09)
A10: J1.52 (BA10)
A11: J1.51 (BA11)
A12: J1.50 (BA12)
A13: J1.49 (BA13)
A14: J1.48 (BA14)
A15: J1.47 (BA15)
CLK: J1.30 (OSC), U2.27 (ϕ2)
D0: J1.40 (DB0), U2.18 (D0)
D1: J1.39 (DB1), U2.19 (D1)
D2: J1.38 (DB2), U2.20 (D2)
D3: J1.37 (DB3), U2.21 (D3)
D4: J1.36 (DB4), U2.22 (D4)
D5: J1.35 (DB5), U2.23 (D5)
D6: J1.34 (DB6), U2.24 (D6)
D7: J1.33 (DB7), U2.25 (D7)
GND: C1.2, C2.2, C3.2, C4.2, C5.2, C6.2, C7.2, C8.2, C9.2, C10.2, J1.1 (GND), J1.10 (GND), J1.31 (GND), J4.4, J5.2, J6.1, J6.3, J6.5, J7.4 (GND), J7.SH (Shield), J9.2, J11.5, J11.6, J11.7, J11.8, J11.10, J11.SH, J12.3, J12.7, J13.3, J14.2 (Ext), U1.10 (GND), U2.1 (VSS), U3.1 (GND), U4.8 (VSS), U4.19 (VSS), U4.27 (A_{VSS})
unnamed: D1.1 (K), R4.1
unnamed: J1.32 (IO), U1.2 (I2), U2.3 (~CS2)
unnamed: J2.1, U2.8 (~RTS)
unnamed: J2.2, U2.9 (~CTS)
unnamed: J3.1, U2.11 (~DTR)
unnamed: J3.2, U2.17 (~DSR)
unnamed: J7.1 (VBUS), J8.3, R5.1
unnamed: F1.1, J8.2
unnamed: J9.1, R4.2, U4.14 (RB5)
unnamed: J10.1, J10.3, J10.5, R6.1
unnamed: J10.2, J11.1
unnamed: J10.4, J11.2
unnamed: J10.6, J11.3
unnamed: J14.1 (In), R9.2, R10.1
unnamed: U1.19 (IO1), U2.2 (CS1)
unnamed: R1.2, U2.6 (XTAL1), Y1.2
unnamed: C3.1, R1.1, U2.7 (XTAL2), Y1.1
unnamed: C4.1, U4.9 (OSC1/RA2), Y2.1
unnamed: C5.1, U4.10 (OSC2/RA3), Y2.2
unnamed: C9.1, U4.20 (VCAP)
unnamed: R5.2, U4.15 (V_{BUS})
~CLK: J1.20 (CLK)
~DMA: J1.6 (DRQ2)
~IO_{W}: J1.13 (~IOW), U2.28 (R/~W)
~IRQ5: J1.23 (IRQ5), U2.26 (~IRQ)
